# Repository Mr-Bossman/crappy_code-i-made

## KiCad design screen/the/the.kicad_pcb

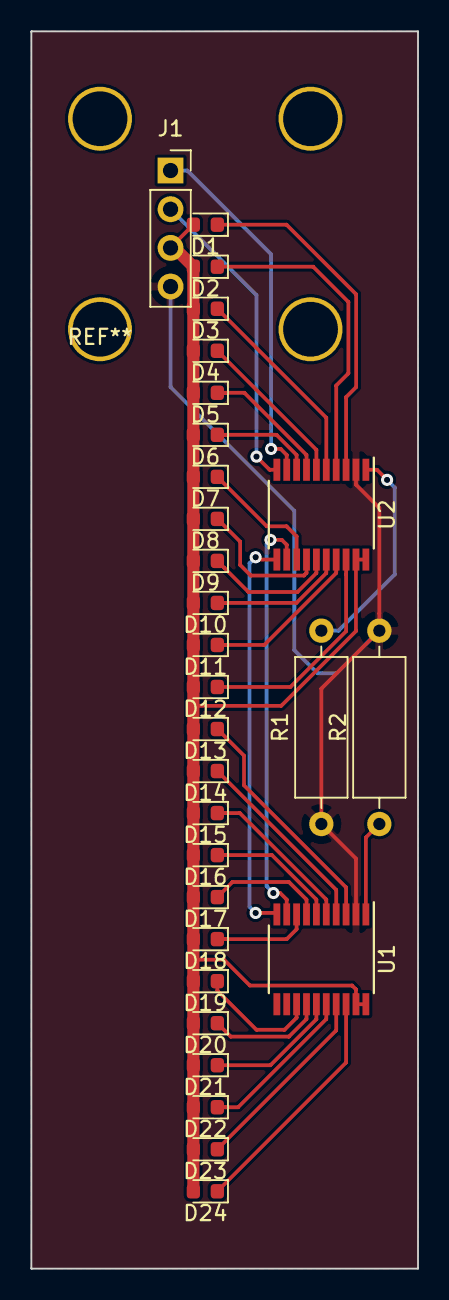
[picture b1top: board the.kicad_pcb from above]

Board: 2 copper layers, 25.4 x 81.3 mm, 29 parts (0 on the bottom side), 32 nets.

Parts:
D1, D2, D3, D4, D5, D6, D7, D8, D9, D10, D11, D12, D13, D14, D15, D16, D17, D18, D19, D20, D21, D22, D23, D24: LED; LED_0603_1608Metric
J1: Conn_01x04_Male; PinSocket_1x04_P2.54mm_Vertical
R1, R2: 3.3k; R_Axial_DIN0309_L9.0mm_D3.2mm_P12.70mm_Horizontal
U1, U2: tlc59711; TSSOP-20_4.4x6.5mm_P0.65mm

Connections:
unnamed: D1.1, U2.3
unnamed: D1.2, D2.2, D3.2, D4.2, D5.2, D6.2, D7.2, D8.2, D9.2, D10.2, D11.2, D12.2, D13.2, D14.2, D15.2, D16.2, D17.2, D18.2, D19.2, D20.2, D21.2, D22.2, D23.2, D24.2, J1.3, U1.19, U1.20, U2.19, U2.20
unnamed: D2.1, U2.4
unnamed: D3.1, U2.5
unnamed: D4.1, U2.6
unnamed: D5.1, U2.7
unnamed: D6.1, U2.8
unnamed: D7.1, U2.13
unnamed: D8.1, U2.14
unnamed: D9.1, U2.15
unnamed: D10.1, U2.16
unnamed: D11.1, U2.17
unnamed: D12.1, U2.18
unnamed: D13.1, U1.3
unnamed: D14.1, U1.4
unnamed: D15.1, U1.5
unnamed: D16.1, U1.6
unnamed: D17.1, U1.7
unnamed: D18.1, U1.8
unnamed: D19.1, U1.13
unnamed: D20.1, U1.14
unnamed: D21.1, U1.15
unnamed: D22.1, U1.16
unnamed: D23.1, U1.17
unnamed: D24.1, U1.18
unnamed: J1.1, U2.9
unnamed: J1.2, U2.10
unnamed: J1.4, R1.1, R2.2, U1.2, U2.2
unnamed: R1.2, U2.1
unnamed: R2.1, U1.1
unnamed: U1.9, U2.12
unnamed: U1.10, U2.11

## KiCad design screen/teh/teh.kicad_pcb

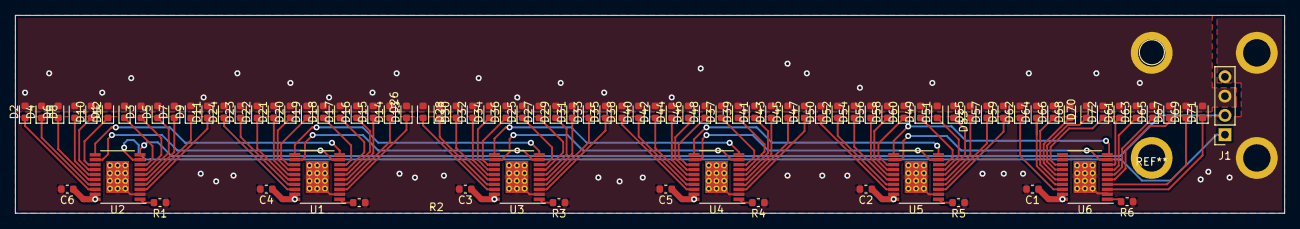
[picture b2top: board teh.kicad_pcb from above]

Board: 2 copper layers, 167.0 x 26.0 mm, 91 parts (0 on the bottom side), 92 nets.

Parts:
C1, C2, C3, C4, C5, C6: C; C_0603_1608Metric
D1, D2, D3, D4, D5, D6, D7, D8, D9, D10, D11, D12, D13, D14, D15, D16, D17, D18, D19, D20, D21, D22, D23, D24, D25, D26, D27, D28, D29, D30, D31, D32, D33, D34, D35, D36, D37, D38, D39, D40, D41, D42, D43, D44, D45, D46, D47, D48, D49, D50, D51, D52, D53, D54, D55, D56, D57, D58, D59, D60, D61, D62, D63, D64, D65, D66, D67, D68, D69, D70, D71, D72: LED; LED_0603_1608Metric
J1: Conn_01x04_Male; PinSocket_1x04_P2.54mm_Vertical
R1, R2, R3, R4, R5, R6: 3.3k; R_0603_1608Metric
U1, U2, U3, U4, U5, U6: tlc59711; ETSSOP-20-1EP_4.4x6.5mm_P0.65mm_EP3x4.2mm_termal

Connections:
GND: C1.2, C2.2, C3.2, C4.2, C5.2, C6.2, J1.4, R1.1, R2.1, R3.1, R4.1, R5.1, R6.1, U1.2, U1.21, U2.2, U2.21, U3.2, U3.21, U4.2, U4.21, U5.2, U5.21, U6.2, U6.21
unnamed: C1.1, C2.1, C3.1, C4.1, C5.1, C6.1, D1.2, D2.2, D3.2, D4.2, D5.2, D6.2, D7.2, D8.2, D9.2, D10.2, D11.2, D12.2, D13.2, D14.2, D15.2, D16.2, D17.2, D18.2, D19.2, D20.2, D21.2, D22.2, D23.2, D24.2, D25.2, D26.2, D27.2, D28.2, D29.2, D30.2, D31.2, D32.2, D33.2, D34.2, D35.2, D36.2, D37.2, D38.2, D39.2, D40.2, D41.2, D42.2, D43.2, D44.2, D45.2, D46.2, D47.2, D48.2, D49.2, D50.2, D51.2, D52.2, D53.2, D54.2, D55.2, D56.2, D57.2, D58.2, D59.2, D60.2, D61.2, D62.2, D63.2, D64.2, D65.2, D66.2, D67.2, D68.2, D69.2, D70.2, D71.2, D72.2, J1.3, U1.19, U1.20, U2.19, U2.20, U3.19, U3.20, U4.19, U4.20, U5.19, U5.20, U6.19, U6.20
unnamed: D1.1, U2.8
unnamed: D2.1, U2.18
unnamed: D3.1, U2.7
unnamed: D4.1, U2.17
unnamed: D5.1, U2.6
unnamed: D6.1, U2.16
unnamed: D7.1, U2.5
unnamed: D8.1, U2.15
unnamed: D9.1, U2.4
unnamed: D10.1, U2.14
unnamed: D11.1, U2.3
unnamed: D12.1, U2.13
unnamed: D13.1, U1.3
unnamed: D14.1, U1.4
unnamed: D15.1, U1.5
unnamed: D16.1, U1.6
unnamed: D17.1, U1.7
unnamed: D18.1, U1.8
unnamed: D19.1, U1.13
unnamed: D20.1, U1.14
unnamed: D21.1, U1.15
unnamed: D22.1, U1.16
unnamed: D23.1, U1.17
unnamed: D24.1, U1.18
unnamed: D25.1, U3.8
unnamed: D26.1, U3.18
unnamed: D27.1, U3.7
unnamed: D28.1, U3.17
unnamed: D29.1, U3.6
unnamed: D30.1, U3.16
unnamed: D31.1, U3.5
unnamed: D32.1, U3.15
unnamed: D33.1, U3.4
unnamed: D34.1, U3.14
unnamed: D35.1, U3.3
unnamed: D36.1, U3.13
unnamed: D37.1, U4.8
unnamed: D38.1, U4.18
unnamed: D39.1, U4.7
unnamed: D40.1, U4.17
unnamed: D41.1, U4.6
unnamed: D42.1, U4.16
unnamed: D43.1, U4.5
unnamed: D44.1, U4.15
unnamed: D45.1, U4.4
unnamed: D46.1, U4.14
unnamed: D47.1, U4.3
unnamed: D48.1, U4.13
unnamed: D49.1, U5.8
unnamed: D50.1, U5.18
unnamed: D51.1, U5.7
unnamed: D52.1, U5.17
unnamed: D53.1, U5.6
unnamed: D54.1, U5.16
unnamed: D55.1, U5.5
unnamed: D56.1, U5.15
unnamed: D57.1, U5.4
unnamed: D58.1, U5.14
unnamed: D59.1, U5.3
unnamed: D60.1, U5.13
unnamed: D61.1, U6.8
unnamed: D62.1, U6.18
unnamed: D63.1, U6.7
unnamed: D64.1, U6.17
unnamed: D65.1, U6.6
unnamed: D66.1, U6.16
unnamed: D67.1, U6.5
unnamed: D68.1, U6.15
unnamed: D69.1, U6.4
unnamed: D70.1, U6.14
unnamed: D71.1, U6.3
unnamed: D72.1, U6.13
unnamed: J1.1, U2.9
unnamed: J1.2, U2.10
unnamed: R1.2, U2.1
unnamed: R2.2, U1.1
unnamed: R3.2, U3.1
unnamed: R4.2, U4.1
unnamed: R5.2, U5.1
unnamed: R6.2, U6.1
unnamed: U1.9, U2.12
unnamed: U1.10, U2.11
unnamed: U1.11, U3.10
unnamed: U1.12, U3.9
unnamed: U3.11, U4.10
unnamed: U3.12, U4.9
unnamed: U4.11, U5.10
unnamed: U4.12, U5.9
unnamed: U5.11, U6.10
unnamed: U5.12, U6.9

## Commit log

2022-01-23 random stuff
